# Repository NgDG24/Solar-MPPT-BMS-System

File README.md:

# Advanced Solar Power Path Manager with MPPT & BMS

- Author: Nguyen Duc Giang

## 📌 Project Overview
This project is a high-efficiency, robust hardware system designed to harvest solar energy (9V, 2.5A) and safely manage the charging/discharging process for a 1-Cell 18650 Li-ion battery. The design focuses on optimizing the "Power Path" through three specialized stages: High-Voltage Surge Protection, MPPT Buck Charging, and precision Battery Management.

## 🛠️ Advanced PCB Layout Techniques Applied
Designing a mixed-signal board that handles high current (3.2A), high-frequency switching (1.5MHz), and micro-volt level sensing requires strict adherence to design rules. This PCB was designed with the following industry-standard techniques:

*   **IPC-2221 Trace Width Compliance:** Power traces carrying up to 3.2A are designed using Polygon Pours (≥ 1.37mm) rather than standard traces to minimize IR drop and effectively dissipate heat generated by the MOSFETs and Inductor.
*   **Kelvin Sensing (4-Wire Measurement):** The current sense resistors (CSP/CSN pins on both LTC4162 and MAX17302) are routed using ultra-thin parallel differential pairs directly from the inner pads of the sense resistor. This prevents the 3.2A load current from interfering with the highly sensitive micro-volt measurements.
*   **Hot-Loop Minimization & Clearance:** The VOUT bypass capacitors for the LTC4162 are placed millimeters away from the IC to minimize parasitic inductance in the high-frequency loop. Additionally, strict clearance zones (> 0.5mm) are enforced around the high-impedance pins (SD, VDD, GATE) of the LTC4366 to prevent micro-amp leakage currents from causing false shutdowns [7].

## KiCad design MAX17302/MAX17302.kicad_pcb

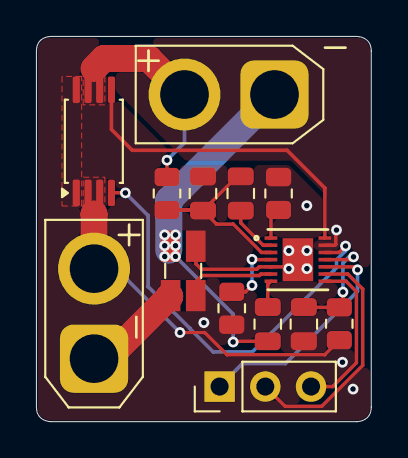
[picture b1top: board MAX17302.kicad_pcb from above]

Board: 2 copper layers, 18.6 x 21.4 mm, 14 parts (0 on the bottom side), 19 nets.

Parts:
C1, C3, C4: 0.1 µF; C_0805_2012Metric
C2: 0.47µF; C_0805_2012Metric
J1, J2: Conn_01x02; AMASS_XT30U-F_1x02_P5.0mm_Vertical
J3: Conn_01x03; PinHeader_1x03_P2.54mm_Vertical
Q3: FS8205A; TSSOP-8_4.4x3mm_P0.65mm
R1: 10Ω; R_0805_2012Metric
R2: 10mΩ; R_Shunt_Ohmite_LVK12
R3, R4: 1k; R_0805_2012Metric
TH1: 10kΩ; R_0805_2012Metric
U1: MAX17302G+T; 21-0137I_T1433-2_MXM

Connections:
/BATT: C1.1, C3.2, R1.1, U1.3 (BATT)
/CELL+: J2.2, Q3.6 (D2), Q3.7 (D1), R1.2
/CELL-: C2.2, J2.1, R2.1
/CHG: Q3.5 (D2), U1.14 (CHG)
/CSN2: R2.3, U1.6 (CSN)
/CSP2: R2.2, U1.5 (CSP), U1.15 (EPAD)
/DIS: Q3.4 (G2), U1.12 (DIS)
/PK+: J1.2, Q3.2 (G1), Q3.3 (S2), R4.1
/PK-: J1.1, R2.4
DRAIN: Q3.1 (S1), Q3.8 (D1)
GND: C3.1, C4.1, R3.1, TH1.1, U1.13 (ZVC)
unnamed: J3.1, U1.10 (ALRT/PIO)
unnamed: J3.2, U1.9 (SCL/OD)
unnamed: J3.3, U1.8 (SDA/DQ)
unnamed: C1.2, U1.2 (CP)
unnamed: C4.2, R4.2, U1.11 (PCKP)
unnamed: R3.2, U1.4 (PFAIL)
unnamed: C2.1, U1.7 (REG)
unnamed: TH1.2, U1.1 (TH)

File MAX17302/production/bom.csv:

Designator,Footprint,Quantity,Value,LCSC Part #
"C1, C3, C4",0805,3,0.1 µF,
C2,0805,1,0.47µF,
"J1, J2",AMASS_XT30U-F_1x02_P5.0mm_Vertical,2,Conn_01x02,
J3,PinHeader_1x03_P2.54mm_Vertical,1,Conn_01x03,
Q3,TSSOP-8_4.4x3mm_P0.65mm,1,FS8205A,
R1,0805,1,10Ω,
R2,R_Shunt_Ohmite_LVK12,1,10mΩ,
"R3, R4",0805,2,1k,
TH1,0805,1,10kΩ,
U1,21-0137I_T1433-2_MXM,1,MAX17302G+T,

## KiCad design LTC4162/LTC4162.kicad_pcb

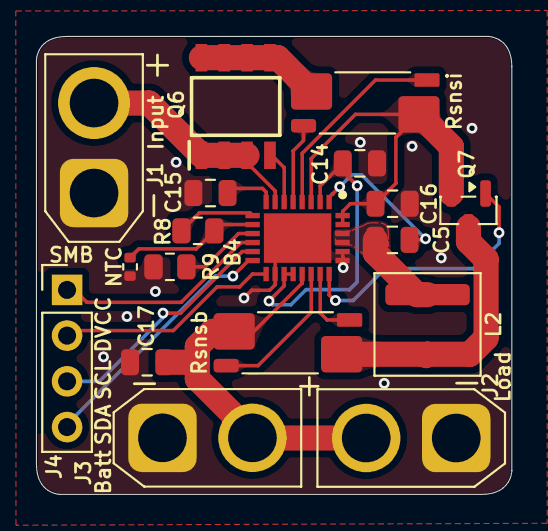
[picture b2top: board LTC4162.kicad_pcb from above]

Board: 2 copper layers, 26.4 x 25.4 mm, 18 parts (0 on the bottom side), 23 nets.

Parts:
B4: LTC4162EUFD-LAD#PBF; QFN50P400X500X80-29N-D
C5: 22nF; C_0805_2012Metric
C14: 4.7µF; C_0805_2012Metric
C15: 1µF; C_0805_2012Metric
C16, C17: 10µF; C_0805_2012Metric
J1: Conn_01x02; AMASS_XT30U-F_1x02_P5.0mm_Vertical
J2, J3: Conn_01x02; AMASS_XT30U-M_1x02_P5.0mm_Vertical
J4: Conn_01x04; PinHeader_1x04_P2.54mm_Vertical
L2: 6.8µH; L_Coilcraft_XAL5030-XXX
NTC: 10k; R_0402_1005Metric
Q6: AO4406A; SOIC127P600X175-8N
Q7: 2N7002; SOT-23
R8: 10k; R_0805_2012Metric
R9: 63.4k; R_0805_2012Metric
Rsnsb: 10mΩ; R_Shunt_Vishay_WSK2512_6332Metric_T1.19mm
Rsnsi: 16mΩ; R_Shunt_Vishay_WSK2512_6332Metric_T1.19mm

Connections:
/PK+: B4.19 (BATSENS+), C17.2, J2.2, J3.2, Rsnsb.4
/Vin LTC4162: B4.7 (VIN), J1.2, Q6.1 (G), Q6.2 (D), Q6.3 (S)
GND: B4.16 (SYNC), B4.23 (PGND_1), B4.24 (PGND_2), B4.29 (AGND), C14.2, C15.1, C16.1, C17.1, J1.1, J2.1, J3.1, NTC.2, R9.1
unnamed: B4.22 (BATFET), Q7.1 (G)
unnamed: B4.1 (BOOST), C5.2
unnamed: B4.2 (INTVCC), B4.17 (CELLS0), B4.18 (CELLS1), C14.1
unnamed: B4.4 (CLN), Rsnsi.2
unnamed: B4.5 (CLP), Rsnsi.3
unnamed: B4.20 (CSN), Rsnsb.3
unnamed: B4.21 (CSP), Rsnsb.2
unnamed: B4.15 (DVCC), J4.2
unnamed: B4.6 (INFET), Q6.4
unnamed: B4.10 (NTC), NTC.1, R8.1
unnamed: B4.9 (NTCBIAS), R8.2
unnamed: B4.11 (RT), R9.2
unnamed: B4.13 (SCL), J4.3
unnamed: B4.14 (SDA), J4.4
unnamed: B4.25 (SW_1), B4.26 (SW_2), C5.1, L2.1
unnamed: B4.8 (VCC2P5), C15.2
unnamed: B4.3 (VOUTA), B4.27 (VOUT_1), B4.28 (VOUT_2), C16.2, Q7.2 (D), Rsnsi.1
unnamed: B4.12 (~SMBALERT), J4.1
unnamed: Q6.5, Q6.6, Q6.7, Q6.8, Rsnsi.4
unnamed: L2.2, Q7.3 (S), Rsnsb.1

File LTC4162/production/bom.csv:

Designator,Footprint,Quantity,Value,LCSC Part #
B4,QFN50P400X500X80-29N-D,1,LTC4162EUFD-LAD#PBF,
C14,0805,1,4.7µF,
C15,0805,1,1µF,
"C16, C17",0805,2,10µF,
C5,0805,1,22nF,
J1,AMASS_XT30U-F_1x02_P5.0mm_Vertical,1,Conn_01x02,
"J2, J3",AMASS_XT30U-M_1x02_P5.0mm_Vertical,2,Conn_01x02,
L2,L_Coilcraft_XAL5030-XXX,1,6.8µH,
NTCS0402E3103FLT2,0402,1,10k,
Q6,SOIC127P600X175-8N,1,AO4406A,
Q7,SOT-23,1,2N7002,
R8,0805,1,10k,
R9,0805,1,63.4k,
RSNSB2,R_Shunt_Vishay_WSK2512_6332Metric_T1.19mm,1,10mΩ,
RSNSI2,R_Shunt_Vishay_WSK2512_6332Metric_T1.19mm,1,16mΩ,

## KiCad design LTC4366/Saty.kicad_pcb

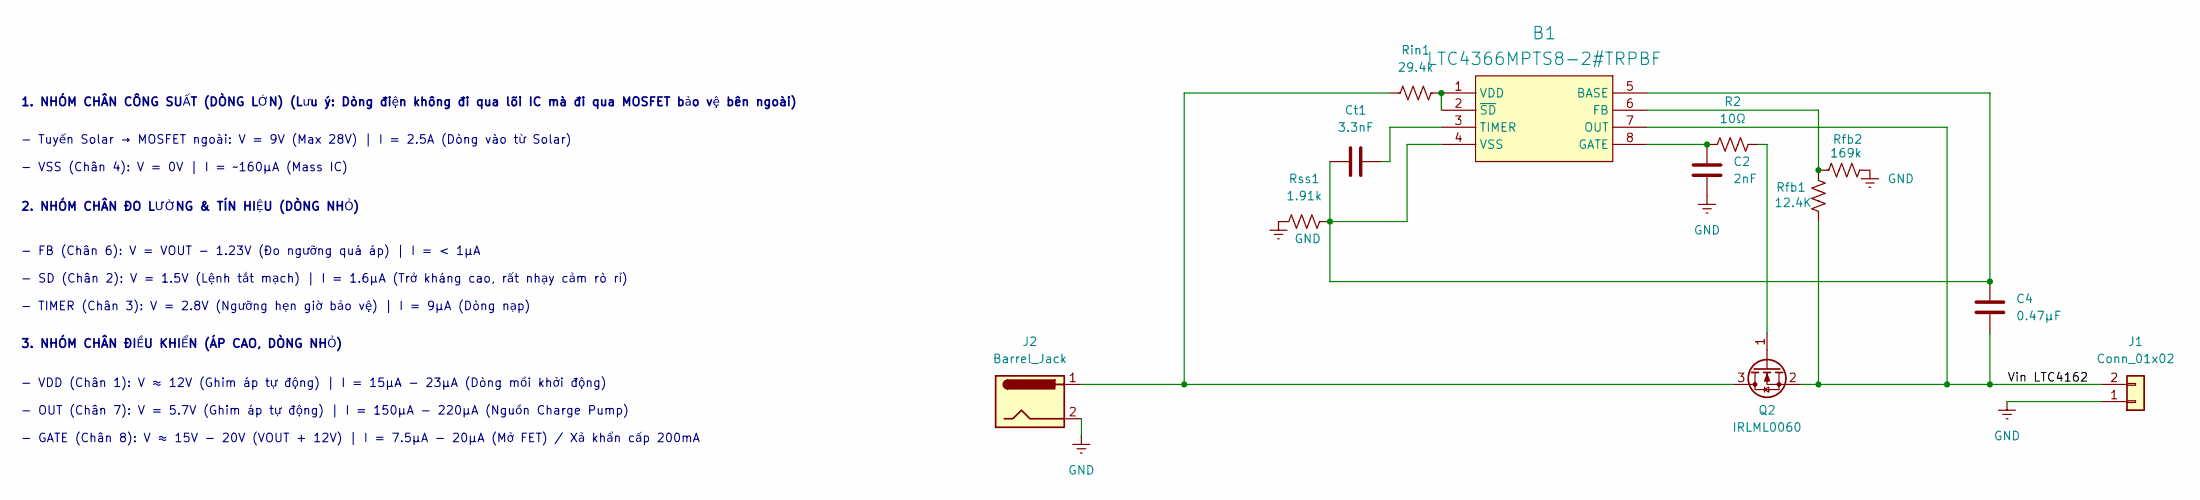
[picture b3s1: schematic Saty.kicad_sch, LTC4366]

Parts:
B1: LTC4366MPTS8-2#TRPBF; SOT65P280X100-8N; Manufacturer_Part_Number LTC4366MPTS8-2#TRPBF; Mouser Part Number 584-C4366MPTS8-2TPF
C2: 2nF; C_0805_2012Metric
C4: 0.47µF; C_0805_2012Metric
Ct1: 3.3nF; C_0805_2012Metric
J1: Conn_01x02; AMASS_XT30UPB-M_1x02_P5.0mm_Vertical
J2: Barrel_Jack; BarrelJack_GCT_DCJ200-10-A_Horizontal
Q2: IRLML0060; SOT-23
R2: 10Ω; R_0805_2012Metric
Rfb1: 12.4K; R_0805_2012Metric
Rfb2: 169k; R_0805_2012Metric
Rin1: 29.4k; R_0805_2012Metric
Rss1: 1.91k; R_0805_2012Metric

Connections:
/Vin LTC4162: B1.7 (OUT), C4.1, J1.2, Q2.2 (S), Rfb1.1
GND: C2.1, J1.1, J2.2, Rfb2.2, Rss1.2
unnamed: B1.4 (VSS), B1.5 (BASE), C4.2, Ct1.1, Rss1.1
unnamed: B1.6 (FB), Rfb1.2, Rfb2.1
unnamed: B1.8 (GATE), C2.2, R2.1
unnamed: B1.3 (TIMER), Ct1.2
unnamed: B1.1 (VDD), B1.2 (~SD), Rin1.1
unnamed: J2.1, Q2.3 (D), Rin1.2
unnamed: Q2.1 (G), R2.2

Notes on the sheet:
3. NHÓM CHÂN ĐIỀU KHIỂN (ÁP CAO, DÒNG NHỎ)
2. NHÓM CHÂN ĐO LƯỜNG & TÍN HIỆU (DÒNG NHỎ)
1. NHÓM CHÂN CÔNG SUẤT (DÒNG LỚN) (Lưu ý: Dòng điện không đi qua lõi IC mà đi qua MOSFET bảo vệ bên ngoài)
- FB (Chân 6): V = VOUT - 1.23V (Đo ngưỡng quá áp) | I = < 1µA - SD (Chân 2): V = 1.5V (Lệnh tắt mạch) | I = 1.6µA (Trở kháng cao, rất nhạy cảm rò rỉ) - TIMER (Chân 3): V = 2.8V (Ngưỡng hẹn giờ bảo vệ) | I = 9µA (Dòng nạp)
- Tuyến Solar → MOSFET ngoài: V = 9V (Max 28V) | I = 2.5A (Dòng vào từ Solar) - VSS (Chân 4): V = 0V | I = ~160µA (Mass IC)
- VDD (Chân 1): V ≈ 12V (Ghim áp tự động) | I = 15µA - 23µA (Dòng mồi khởi động) - OUT (Chân 7): V = 5.7V (Ghim áp tự động) | I = 150µA - 220µA (Nguồn Charge Pump) - GATE (Chân 8): V ≈ 15V - 20V (VOUT + 12V) | I = 7.5µA - 20µA (Mở FET) / Xả khẩn cấp 200mA

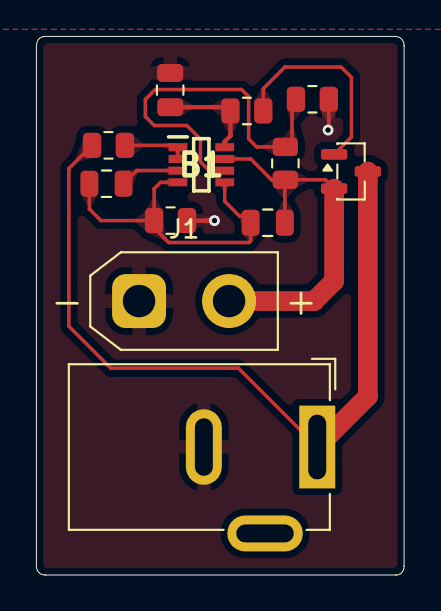
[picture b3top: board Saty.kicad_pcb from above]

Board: 2 copper layers, 20.4 x 29.9 mm, 12 parts (0 on the bottom side), 9 nets.

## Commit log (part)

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2026-06-30 Revise README with enhanced project details
    Updated project title and expanded project overview with detailed hardware architecture and PCB layout techniques.
